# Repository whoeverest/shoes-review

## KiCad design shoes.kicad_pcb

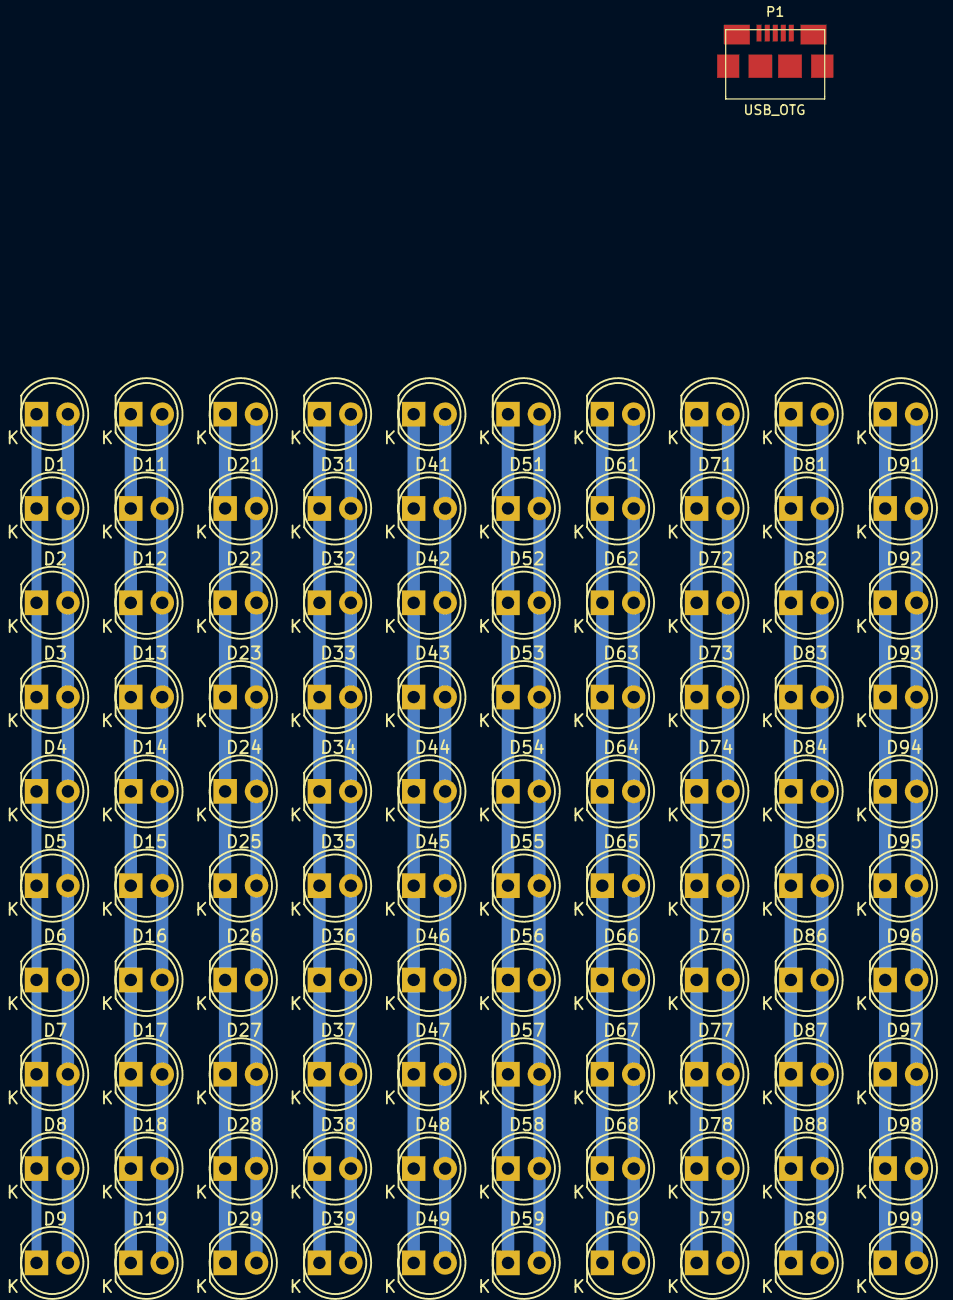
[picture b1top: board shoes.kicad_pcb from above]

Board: 2 copper layers, 101 parts (0 on the bottom side), 3 nets.

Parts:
D1, D2, D3, D4, D5, D6, D7, D8, D9, D10, D11, D12, D13, D14, D15, D16, D17, D18, D19, D20, D21, D22, D23, D24, D25, D26, D27, D28, D29, D30, D31, D32, D33, D34, D35, D36, D37, D38, D39, D40, D41, D42, D43, D44, D45, D46, D47, D48, D49, D50, D51, D52, D53, D54, D55, D56, D57, D58, D59, D60, D61, D62, D63, D64, D65, D66, D67, D68, D69, D70, D71, D72, D73, D74, D75, D76, D77, D78, D79, D80, D81, D82, D83, D84, D85, D86, D87, D88, D89, D90, D91, D92, D93, D94, D95, D96, D97, D98, D99, D100: LED; LED-5MM
P1: USB_OTG; MICRO-B_USB

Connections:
GND: D1.1, D2.1, D3.1, D4.1, D5.1, D6.1, D7.1, D8.1, D9.1, D10.1, D11.1, D12.1, D13.1, D14.1, D15.1, D16.1, D17.1, D18.1, D19.1, D20.1, D21.1, D22.1, D23.1, D24.1, D25.1, D26.1, D27.1, D28.1, D29.1, D30.1, D31.1, D32.1, D33.1, D34.1, D35.1, D36.1, D37.1, D38.1, D39.1, D40.1, D41.1, D42.1, D43.1, D44.1, D45.1, D46.1, D47.1, D48.1, D49.1, D50.1, P1.5
unnamed: D1.2, D2.2, D3.2, D4.2, D5.2, D6.2, D7.2, D8.2, D9.2, D10.2, D11.2, D12.2, D13.2, D14.2, D15.2, D16.2, D17.2, D18.2, D19.2, D20.2, D21.2, D22.2, D23.2, D24.2, D25.2, D26.2, D27.2, D28.2, D29.2, D30.2, D31.2, D32.2, D33.2, D34.2, D35.2, D36.2, D37.2, D38.2, D39.2, D40.2, D41.2, D42.2, D43.2, D44.2, D45.2, D46.2, D47.2, D48.2, D49.2, D50.2, D51.1, D52.1, D53.1, D54.1, D55.1, D56.1, D57.1, D58.1, D59.1, D60.1, D61.1, D62.1, D63.1, D64.1, D65.1, D66.1, D67.1, D68.1, D69.1, D70.1, D71.1, D72.1, D73.1, D74.1, D75.1, D76.1, D77.1, D78.1, D79.1, D80.1, D81.1, D82.1, D83.1, D84.1, D85.1, D86.1, D87.1, D88.1, D89.1, D90.1, D91.1, D92.1, D93.1, D94.1, D95.1, D96.1, D97.1, D98.1, D99.1, D100.1
VCC: D51.2, D52.2, D53.2, D54.2, D55.2, D56.2, D57.2, D58.2, D59.2, D60.2, D61.2, D62.2, D63.2, D64.2, D65.2, D66.2, D67.2, D68.2, D69.2, D70.2, D71.2, D72.2, D73.2, D74.2, D75.2, D76.2, D77.2, D78.2, D79.2, D80.2, D81.2, D82.2, D83.2, D84.2, D85.2, D86.2, D87.2, D88.2, D89.2, D90.2, D91.2, D92.2, D93.2, D94.2, D95.2, D96.2, D97.2, D98.2, D99.2, D100.2, P1.1

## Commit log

2016-01-08 init
2016-01-08 save after annotate
2016-01-08 bakar and wires and shit
2016-01-08 Andrej's turn!
2016-01-08 WIP: added tracks
